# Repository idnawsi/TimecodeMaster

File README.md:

# TimecodeMaster

A wireless SMPTE linear timecode (LTC) generator for film and video sets, built from two ESP32 modules per unit. One master unit holds the time; up to ten client units are jammed to it over ESP-NOW and then run independently on their own TCXO-referenced clock. Each unit produces an LTC audio signal on a 3.5 mm jack for a camera or recorder.

This repository holds everything needed to build and run the system: the KiCad design for the master board, the firmware for all four ESP32 images, and two desktop tools for working with recorded LTC.

| Top (3D render) | Bottom (3D render) |
|---|---|
|  |  |

Board layout views (front, back, and each copper layer) are in [hardware/README.md](hardware/README.md#board-views).

## Frame rates

| Rate | Drop frame | Sample clock | Samples per LTC bit |
|---|---|---|---|
| 23.976 | no | 47952.048 Hz | 25 |
| 24 | no | 48000 Hz | 25 |
| 25 | no | 48000 Hz | 24 |
| 29.97 | selectable | 47952.048 Hz | 20 |
| 30 | no | 48000 Hz | 20 |

The non-integer rates are not approximated. The sample clock itself is divided by 1001, so the LTC frame period is exact and a whole number of samples fits in every bit cell. See [docs/timing.md](docs/timing.md).

## How it works, in short

1. A 25 MHz TCXO feeds an Si5351 clock generator. Its PLL runs at 768 MHz, and a single integer divider produces either 48000 Hz or 47952.048 Hz.
2. That clock is wired to an interrupt pin on the LTC ESP32. Every rising edge writes one sample to the DAC. The bit pattern of the current LTC frame is stepped one sample at a time, so the output frequency is the Si5351 frequency and nothing else.
3. The second ESP32 (the Utility device) runs the Wi-Fi access point and web interface, programs the Si5351, reads the RTC, and talks to the LTC device over SPI.
4. The master sends the time to each client over ESP-NOW, aligned to an LTC frame boundary. After that, every unit keeps time from its own TCXO. Wireless traffic does not steer the clock.
5. A unit can also jam-sync to an external LTC signal fed into the same 3.5 mm jack.

The full description is in [docs/how-it-works.md](docs/how-it-works.md).

The full schematic is in [hardware/docs/schematic.pdf](hardware/docs/schematic.pdf) and the board outputs in [hardware/](hardware/).

## LTC Sync App

During the shoot, each unit records the same LTC onto a camera or recorder audio channel. In post, the [LTC Sync App](docs/ltc-sync-app.md) reads that LTC from the files, places every clip on one timeline by its timecode, and exports the timeline to DaVinci Resolve, Premiere Pro or Final Cut Pro X. It reads the date and a two-digit camera ID that the units write into the LTC user bits, handles 23.976 and 29.97 exactly, and can correct per-camera offsets and a recorder's clock drift. Usage is described in [docs/ltc-sync-app.md](docs/ltc-sync-app.md).

## Repository layout

| Path | Contents |
|---|---|
| [hardware/](hardware/) | KiCad projects (main board, button boards), schematic PDF, BOM, released Gerbers, STEP models |
| [firmware/](firmware/) | Four Arduino sketches: master LTC, master Utility, client LTC, client Utility |
| [software/ltc-sync-app/](software/ltc-sync-app/) | Desktop app that reads LTC from video and audio files, aligns clips, and exports timelines |
| [software/ltc-analyzer/](software/ltc-analyzer/) | Desktop tool that decodes LTC from a live input or a file and reports continuity and drift |
| [docs/](docs/) | Architecture, timing, hardware notes, pinout, protocols, build and operation guides |

## Documentation

| Document | Subject |
|---|---|
| [docs/how-it-works.md](docs/how-it-works.md) | Architecture, clocking, synchronisation, jam sync, power |
| [docs/timing.md](docs/timing.md) | LTC format, non-integer frame rates, drop frame, drift budget |
| [docs/hardware.md](docs/hardware.md) | Circuit description of the master board |
| [docs/pinout.md](docs/pinout.md) | GPIO assignments for every ESP32 image, connector pinouts |
| [docs/protocol.md](docs/protocol.md) | SPI link, ESP-NOW messages, HTTP and WebSocket interface |
| [docs/firmware.md](docs/firmware.md) | Toolchain, libraries, build, first flash, over-the-air updates |
| [docs/operation.md](docs/operation.md) | Pairing, syncing, buttons, jam sync, battery, troubleshooting |
| [docs/ltc-sync-app.md](docs/ltc-sync-app.md) | Using the LTC Sync App to align footage and export timelines |
| [docs/design-notes.md](docs/design-notes.md) | Why the classic ESP32 was used (cost and the DAC), why the DAC ended up unused, and what an ESP32-S3 would change |
| [docs/field-test.md](docs/field-test.md) | One real shoot: what the LTC Sync App read from the files |
| [docs/security.md](docs/security.md) | Wi-Fi password, web interface, ESP-NOW and OTA: what is and is not protected |
| [hardware/README.md](hardware/README.md) | Design files, BOM, fabrication status |

## Quick start

Requirements: Arduino IDE 2.x or `arduino-cli`, the `esp32` board package (3.x), and the libraries listed in [docs/firmware.md](docs/firmware.md).

1. Build and flash the two master images (`master_LTC_Device_Jamsync` to the LTC module, `Master_Utility_Device_JamSync_Wireless` to the Utility module). Use board "ESP32 Dev Module" and the "Default 4MB with spiffs" partition scheme.
2. Build and flash the two client images the same way (`Client_LTC_Device`, `Client_Utility_Device_Wireless`).
3. Power the master. Join the Wi-Fi network `TimecodeMaster-XXXX`, open `http://192.168.4.1`, and start pairing.
4. Power a client, confirm it on the master page, and press Sync.

Details, including the password and button gestures, are in [docs/operation.md](docs/operation.md).

## Status

- Firmware version 1.3.37 for the master Utility image and 1.3.34 for the other three. See [CHANGELOG.md](CHANGELOG.md).
- The main board is now Rev 4.2. The KiCad sources in `hardware/kicad/main-board` and the Gerbers in `hardware/fabrication/main-board-rev4.2` are Rev 4.2; the Rev 4.2 set has not been used for an order yet. The released Rev 4.1 Gerbers are kept in `hardware/fabrication/main-board-rev4.1`. See [hardware/README.md](hardware/README.md).
- The current KiCad source adds an ESD diode (D4) and a series resistor (R48) on the LTC I/O jack. The Rev 4.1 Gerbers do not include them; the Rev 4.2 set does. The microphone jack and the LTC jack's ring contact are not protected.
- Only the master board has a PCB design in this repository. The client firmware targets the same two-ESP32 architecture, but its Utility image uses a few different GPIOs (see [docs/pinout.md](docs/pinout.md)).
- The firmware has little security. The web interface has no login, ESP-NOW is unencrypted, and the OTA password is a fixed string. See [docs/security.md](docs/security.md).
- The firmware has not been certified against any broadcast standard. Check the output against your own equipment, for example with the LTC Analyzer in this repository.

## Authorship

The firmware in this repository was written by AI. The hardware (schematic and PCB) was designed by me, and the testing of the units was done by me. Read the firmware with that in mind and check it on your own hardware before relying on it.

## License

Source-available under the [PolyForm Noncommercial License 1.0.0](LICENSE), with an [additional permission](ADDITIONAL-PERMISSION.md). Personal, hobby, study and other noncommercial use is free. Small independent users (total business revenue under US$100,000 a year, for example photographers, videographers and indie filmmakers) may also use it on their own paid work for free. Everyone else using it commercially, and anyone selling or renting units, boards, firmware or software, needs a separate paid license. See [COMMERCIAL.md](COMMERCIAL.md). This is not an OSI-approved open source license.

Required notice: see [NOTICE](NOTICE). Material from other people (KiCad and part libraries, the libraries the firmware needs) keeps its own terms; see [THIRD-PARTY.md](THIRD-PARTY.md).

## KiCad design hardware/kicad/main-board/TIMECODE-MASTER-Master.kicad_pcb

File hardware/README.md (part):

# Hardware

KiCad 9 design files, outputs and manufacturing data for the TimecodeMaster main board and its two small accessory boards. The circuit is described in [../docs/hardware.md](../docs/hardware.md) and the pin assignments in [../docs/pinout.md](../docs/pinout.md).

The schematic as a PDF: [docs/schematic.pdf](docs/schematic.pdf). Board views are below.

## Board views

3D renders from KiCad (top and bottom):

| Top | Bottom |
|---|---|
|  |  |

Layout views (copper, mask and silkscreen). The back view is mirrored, as seen from the back of the board:

Individual copper layers (the back layer is mirrored):

| Front (F.Cu) | Inner 1 (In1.Cu) |
|---|---|
|  |  |

| Inner 2 (In2.Cu) | Back (B.Cu) |
|---|---|
|  |  |

All views come from the current PCB source (Rev 4.2), not from the Rev 4.1 Gerbers (see Fabrication status below).

## Contents

| Path | Contents |
|---|---|
| `kicad/main-board/` | Project, schematic and PCB of the master board (title block "TimeCode-Master") |
| `kicad/control-button-board/` | Four tactile switches (FPS, LEVEL, WIFI, SYNC) and the 5-pin connector that plugs into J4 |
| `kicad/power-switch-board/` | The slide power switch (TL2285EE) on the `G-Switch` net |
| `fabrication/main-board-rev4.1/` | Gerber and drill files of the released Rev 4.1 boards, generated 2026-02-10 with KiCad 9.0.5 |
| `fabrication/main-board-rev4.2/` | Gerber and drill files of Rev 4.2, plotted from the current source on 2026-11-20 with KiCad 9.0.5 |
| `fabrication/control-button-board/`, `fabrication/power-switch-board/` | Gerber and drill files for the accessory boards |
| `cad/` | STEP models of the main board and the button boards |
| `docs/` | Schematic (PDF, SVG) and board renders |
| `bom.csv` | Bill of materials for the main board, generated from the schematic |
| `scripts/` | `export.sh` regenerates the PDF, SVG, renders and BOM; `make_bom.py` builds the BOM from a netlist |

## Board

| Item | Value |
|---|---|
| Size | 70.04 x 50.54 mm |
| Layers | 4 (F.Cu, In1.Cu, In2.Cu, B.Cu), 1.6 mm |
| Minimum track / space (released Gerbers) | 0.127 mm |
| Main parts | 2 x ESP32-WROOM-32E, Si5351A, 25 MHz TCXO, DS3231M, ADS1115, TPS63070, TP4056, OPA365 |
| Mounting | 4 x M2.5 holes |

Symbols and footprints, including the custom ones (TSX-3225, SMF05C, PJ-342B, the RGB LED, the TL2285EE switch), are embedded in the schematic and board files.

## Fabrication status

Two Gerber sets are kept:

- `fabrication/main-board-rev4.1` was released on 2026-02-10. It does not match the current source and is kept for reference.
- `fabrication/main-board-rev4.2` is Rev 4.2, plotted from the current source in `kicad/main-board` on 2026-11-20 (4 layers, 70.04 x 50.54 mm, outline unchanged). The board silkscreen reads Rev4.2. The set has not been used for an order.

What changed from Rev 4.1 to Rev 4.2:

- D4 (ESD diode) and R48 (1 kOhm) on the LTC I/O jack, and the OPA365 (U16) instead of the OPA1656.
- The 10 uF radial capacitors C18 and C21 now have a 1.5 mm lead pitch and 0.6 mm holes (Rev 4.1: 2.5 mm pitch, 0.8 mm holes). Buy 4 mm radial capacitors with 1.5 mm leads.
- The via drill mix differs (0.33 mm now appears, 50 holes), and the plated hole count went from 387 to 414.
- A stray 100 nF footprint labelled C28 was removed.

Before ordering from either set:

1. Open `kicad/main-board/TIMECODE-MASTER-Master.kicad_pcb` and run the design rule check (13 items today, listed below).
2. Re-plot if you change anything (the commands are in `scripts/export.sh`). Check the files in a Gerber viewer and with your manufacturer's own checker.
3. The BOM, pin tables and schematic PDF in this repository match Rev 4.2, not Rev 4.1.

## Known limitations

The design is published as it stands. These are the open points, recorded so that nobody has to find them again.

- **Jack protection is partial.** The current source has an ESD diode (D4, PESD5V0S1BA) and a 1 kOhm series resistor (R48) on the tip of the LTC I/O jack. The ring contact of that jack (U14 pin 3, through S1) and the microphone jack U13 have no protection. The Rev 4.1 boards have none of it.
- **Rev 4.1 and Rev 4.2 differ.** The Gerbers in `fabrication/main-board-rev4.1` are the Rev 4.1 set; Rev 4.2 has its own (see Fabrication status). Rev 4.2 adds D4 and R48 and replaces the OPA1656 microphone preamp with an OPA365 (U16). The OPA1656 needs at least 4.5 V and runs from a 3.3 V rail on Rev 4.1; the microphone path is not used by the firmware, so nothing depends on it.
- **MIC output level.** It is set by a resistor divider and cannot be changed in firmware. R48 takes roughly 1 to 3 dB off it. Raise the camera gain or change R16 if a camera needs more.
- **Design rule check.** 13 items: 11 copper-to-edge clearance (corner mounting holes and R10 on the back) and 2 courtyard overlaps (U12 with MH1, D4 with U10).
- **Q1 and Q2** drive CD4066 control pins with no pull-down, and the Utility wake divider gives 2.5 V. See [docs/hardware.md](../docs/hardware.md).

## Bill of materials (main board)

Generated from the current schematic by `scripts/make_bom.py`. Passive values are as drawn; confirm tolerances and voltage ratings when sourcing. The part list contains no manufacturer part numbers for passives.

| Qty | References | Value | Footprint | Function |
|---:|---|---|---|---|
| 1 | U1 | CD4066BM | SO-14_3.9x8.65mm_P1.27mm | Quad analog switch (LINE/MIC level, LTC jack direction) |
| 1 | U2 | SMF05CT1G | SOT65P210X110-6N | USB ESD / TVS array |
| 1 | U3 | DS3231M | SOIC-16W_7.5x10.3mm_P1.27mm | Real-time clock with integrated TCXO |
| 1 | U4 | 74HC14 | SOIC-14_3.9x8.7mm_P1.27mm | Hex Schmitt-trigger inverter (LTC output buffer, input conditioning) |
| 1 | U5 | TP4056-42-ESOP8 | SOIC-8-1EP_3.9x4.9mm_P1.27mm_EP2.41x3.3mm_ThermalVias | Li-ion linear charger, 1 A max |
| 1 | U6 | FS8205A-SOT23 | TSOT-23-6_HandSoldering | Dual N-channel MOSFET (battery protection switch) |
| 1 | U7 | DW01A | SOT-23-6 | Li-ion protection controller |
| 1 | U8 | RT9013-33GB | SOT94P279X129-5N | 3.3 V LDO (500 mA), analog rail |
| 1 | U10 | LTC-DEVICE | ESP32-WROOM-32E | ESP32-WROOM-32E module: LTC device |
| 1 | U11 | TPS63070RNMR | VREG_TPS63070RNMR | Buck-boost converter, 3.3 V system rail |
| 1 | U12 | UTILITY-DEVICE | ESP32-WROOM-32E | ESP32-WROOM-32E module: Utility device |
| 2 | U13, U14 | PJ-342B | PJ-342B | 3.5 mm jacks: U13 microphone output, U14 LTC I/O |
| 1 | U15 | ADS1115IDGS | TSSOP-10_3x3mm_P0.5mm | 16-bit I2C ADC (battery voltage) |
| 1 | U16 | OPA365xxDBV | SOT-23-5 | Single rail-to-rail op-amp, 2.2 to 5.5 V (microphone preamp) |
| 1 | X1 | 25MHZ 0.5ppm TCXO | TSX-3225 | 25 MHz 0.5 ppm TCXO |
| 1 | Y1 | Si5351A-B-GT | MSOP-10_3x3mm_P0.5mm | I2C programmable clock generator |
| 4 | Q1-Q4 | AO3407 | SOT-23 | P-channel MOSFET, SOT-23 (Q1, Q2 level control; Q3 power switch; Q4 battery path) |
| 1 | D1 | OSTB0805C1C-A | LEDSC200X125X110-4N | Bi-colour LED (charge / standby) |
| 1 | D2 | SS14 | D_SMA | Schottky diode (USB to supply OR-ing) |
| 1 | D3 | Blue_Led | LED_0805_2012Metric | Blue status LED (Utility GPIO2) |
| 1 | D4 | PESD5V0S1BA | D_SOD-323 | Bidirectional ESD diode on the LTC jack tip (R48 limits current behind it) |
| 1 | J1 | USB_C_Receptacle_PowerOnly_6P | USB_C_Receptacle_HRO_TYPE-C-31-M-17 | USB-C receptacle, power only |
| 1 | J2 | S8421-45R | 2 Pad | RTC backup battery pads |
| 1 | J3 | SSD1306 oled | 4 Pad | OLED connector (SSD1306, I2C) |
| 1 | J4 | Conn_01x05_MountingPin | JST_PH_S5B-PH-SM4-TB_1x05-1MP_P2.00mm_Horizontal | Button board connector |
| 1 | S1 | SSSS811101 | SW_SSSS811101 | Slide switch (jack routing) |
| 1 | L1 | 1.5uH | L_7.3x7.3_H4.5 | 1.5 uH power inductor |
| 13 | C1, C3, C4, C6, C10, C13-C15, C19, C22, C25-C27 | 100nF | C_0402_1005Metric_Pad0.74x0.62mm_HandSolder | Capacitor |
| 5 | C2, C5, C9, C12, C16 | 10uF | C_0805_2012Metric | Capacitor |
| 1 | C7 | 10uF | C_0805_2012Metric_Pad1.18x1.45mm_HandSolder | Capacitor |
| 1 | C8 | 10nF | C_0805_2012Metric | Capacitor |
| 3 | C11, C29, C31 | 22uF | C_0805_2012Metric_Pad1.18x1.45mm_HandSolder | Capacitor |
| 1 | C17 | 10uF | C_0402_1005Metric_Pad0.74x0.62mm_HandSolder | Capacitor |
| 2 | C18, C21 | 10uf | C_Radial_D4.0mm_H5.0mm_P1.50mm | Capacitor |
| 1 | C20 | 10pf | C_0402_1005Metric_Pad0.74x0.62mm_HandSolder | Capacitor |
| 2 | C23, C24 | 100uF | CP_EIA-3528-21_Kemet-B_HandSolder | Capacitor |
| 1 | C28 | 1uF | C_0402_1005Metric_Pad0.74x0.62mm_HandSolder | Capacitor |
| 1 | C30 | 1000uF | CP_Elec_8x10 | Capacitor |
| 8 | R1, R3, R25, R26, R39, R43, R44, R47 | 4.7k | R_0402_1005Metric_Pad0.72x0.64mm_HandSolder | Resistor |
| 2 | R2, R4 | 5K1 | R_0402_1005Metric_Pad0.72x0.64mm_HandSolder | Resistor |
| 5 | R5, R8, R14, R16, R48 | 1K | R_0402_1005Metric_Pad0.72x0.64mm_HandSolder | Resistor |
| 6 | R6, R27, R35, R37, R40, R41 | 100k | R_0402_1005Metric_Pad0.72x0.64mm_HandSolder | Resistor |
| 1 | R7 | 68K | R_0402_1005Metric_Pad0.72x0.64mm_HandSolder | Resistor |
| 10 | R9, R18, R19, R23, R28, R30, R31, R33, R45, R46 | 20k | R_0402_1005Metric_Pad0.72x0.64mm_HandSolder | Resistor |
| 1 | R10 | 1.2K | R_0402_1005Metric_Pad0.72x0.64mm_HandSolder | Resistor |
| 1 | R11 | 10R | R_0805_2012Metric | Resistor |
| 1 | R12 | 100R | R_0805_2012Metric | Resistor |
| 2 | R13, R15 | 15K | R_0402_1005Metric_Pad0.72x0.64mm_HandSolder | Resistor |
| 2 | R17, R34 | 10k | R_0402_1005Metric_Pad0.72x0.64mm_HandSolder | Resistor |
| 1 | R20 | 47K | R_0402_1005Metric_Pad0.72x0.64mm_HandSolder | Resistor |
| 1 | R21 | 20R | R_0402_1005Metric_Pad0.72x0.64mm_HandSolder | Resistor |
| 1 | R22 | 100K | R_0402_1005Metric | Resistor |
| 2 | R24, R42 | 10k | R_0402_1005Metric | Resistor |
| 1 | R29 | 150k | R_0402_1005Metric_Pad0.72x0.64mm_HandSolder | Resistor |
| 1 | R32 | 470k | R_0402_1005Metric_Pad0.72x0.64mm_HandSolder | Resistor |
| 1 | R36 | 100R | R_0402_1005Metric_Pad0.72x0.64mm_HandSolder | Resistor |
| 1 | R38 | 47R | R_0402_1005Metric_Pad0.72x0.64mm_HandSolder | Resistor |
| 1 | BT1 | Battery_Cell | 2 Pad | Li-ion cell |
| 3 | FB1-FB3 | 600Ohm/1Mhz | L_0603_1608Metric_Pad1.05x0.95mm_HandSolder | Ferrite bead |
| 1 | JP1 | SolderJumper_2_Open | SolderJumper-2_P1.3mm_Open_Pad1.0x1.5mm | Solder jumper: converter power-save mode |
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
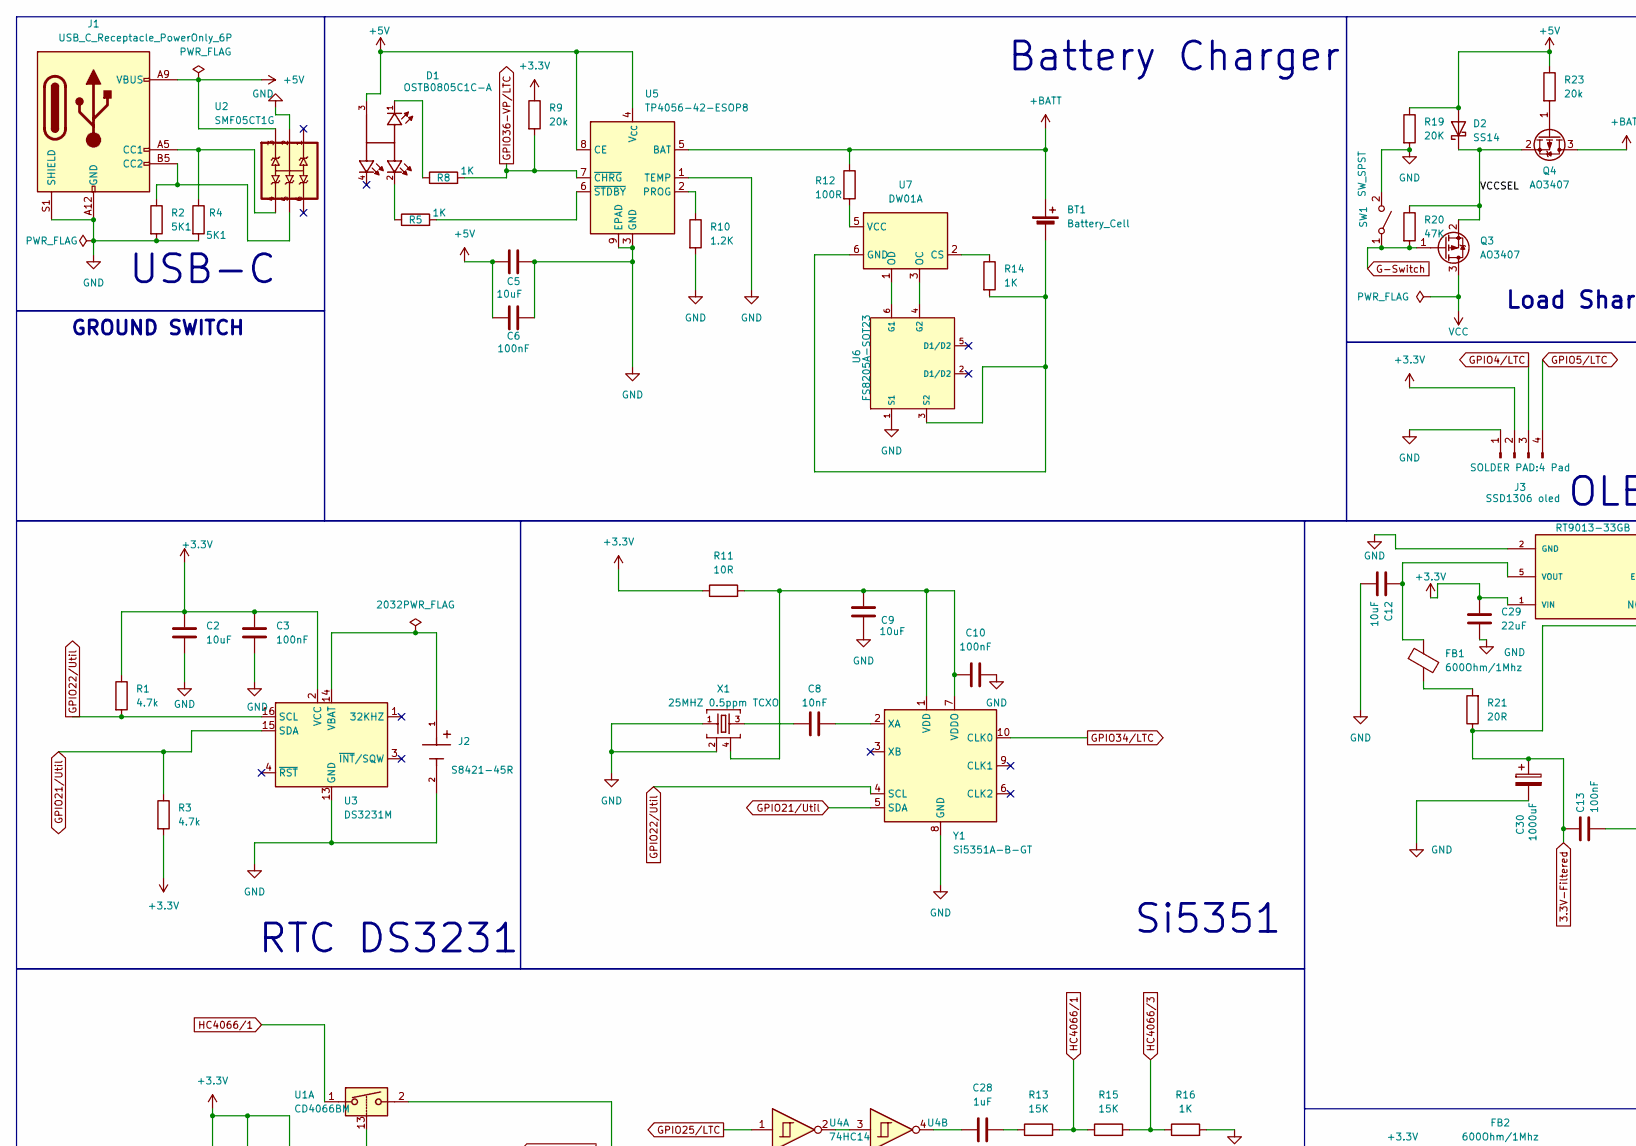
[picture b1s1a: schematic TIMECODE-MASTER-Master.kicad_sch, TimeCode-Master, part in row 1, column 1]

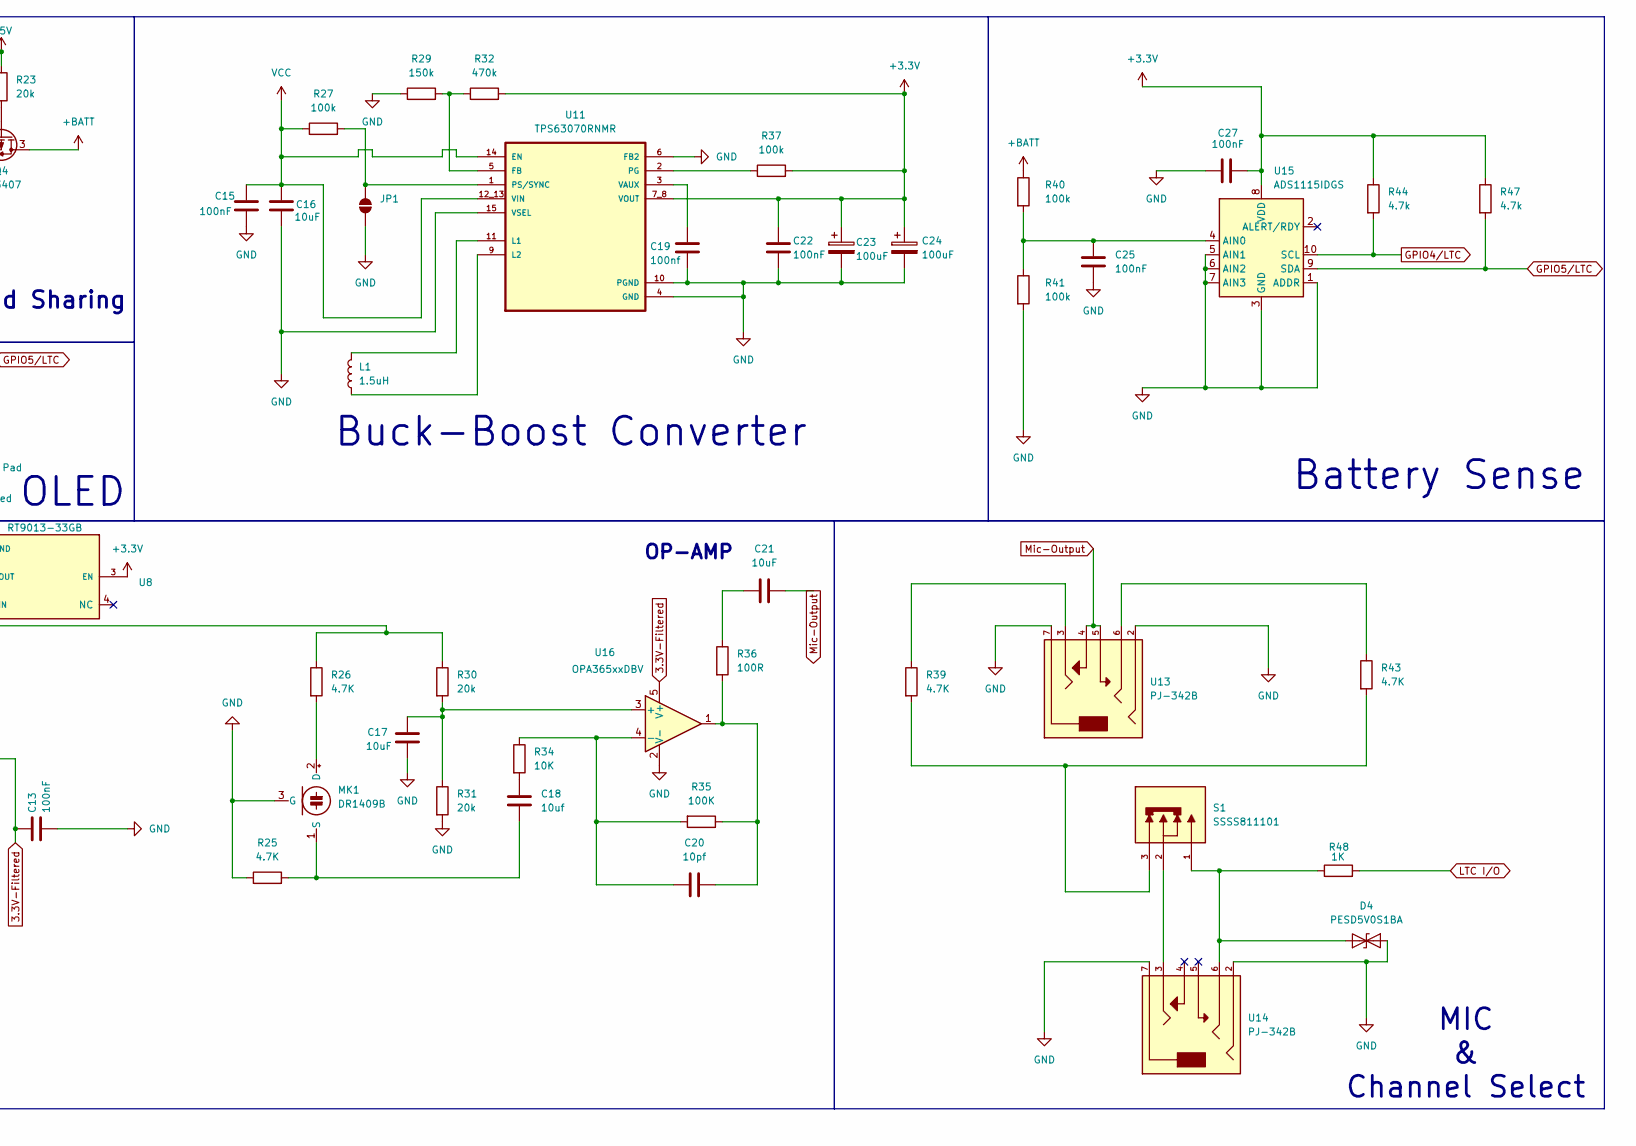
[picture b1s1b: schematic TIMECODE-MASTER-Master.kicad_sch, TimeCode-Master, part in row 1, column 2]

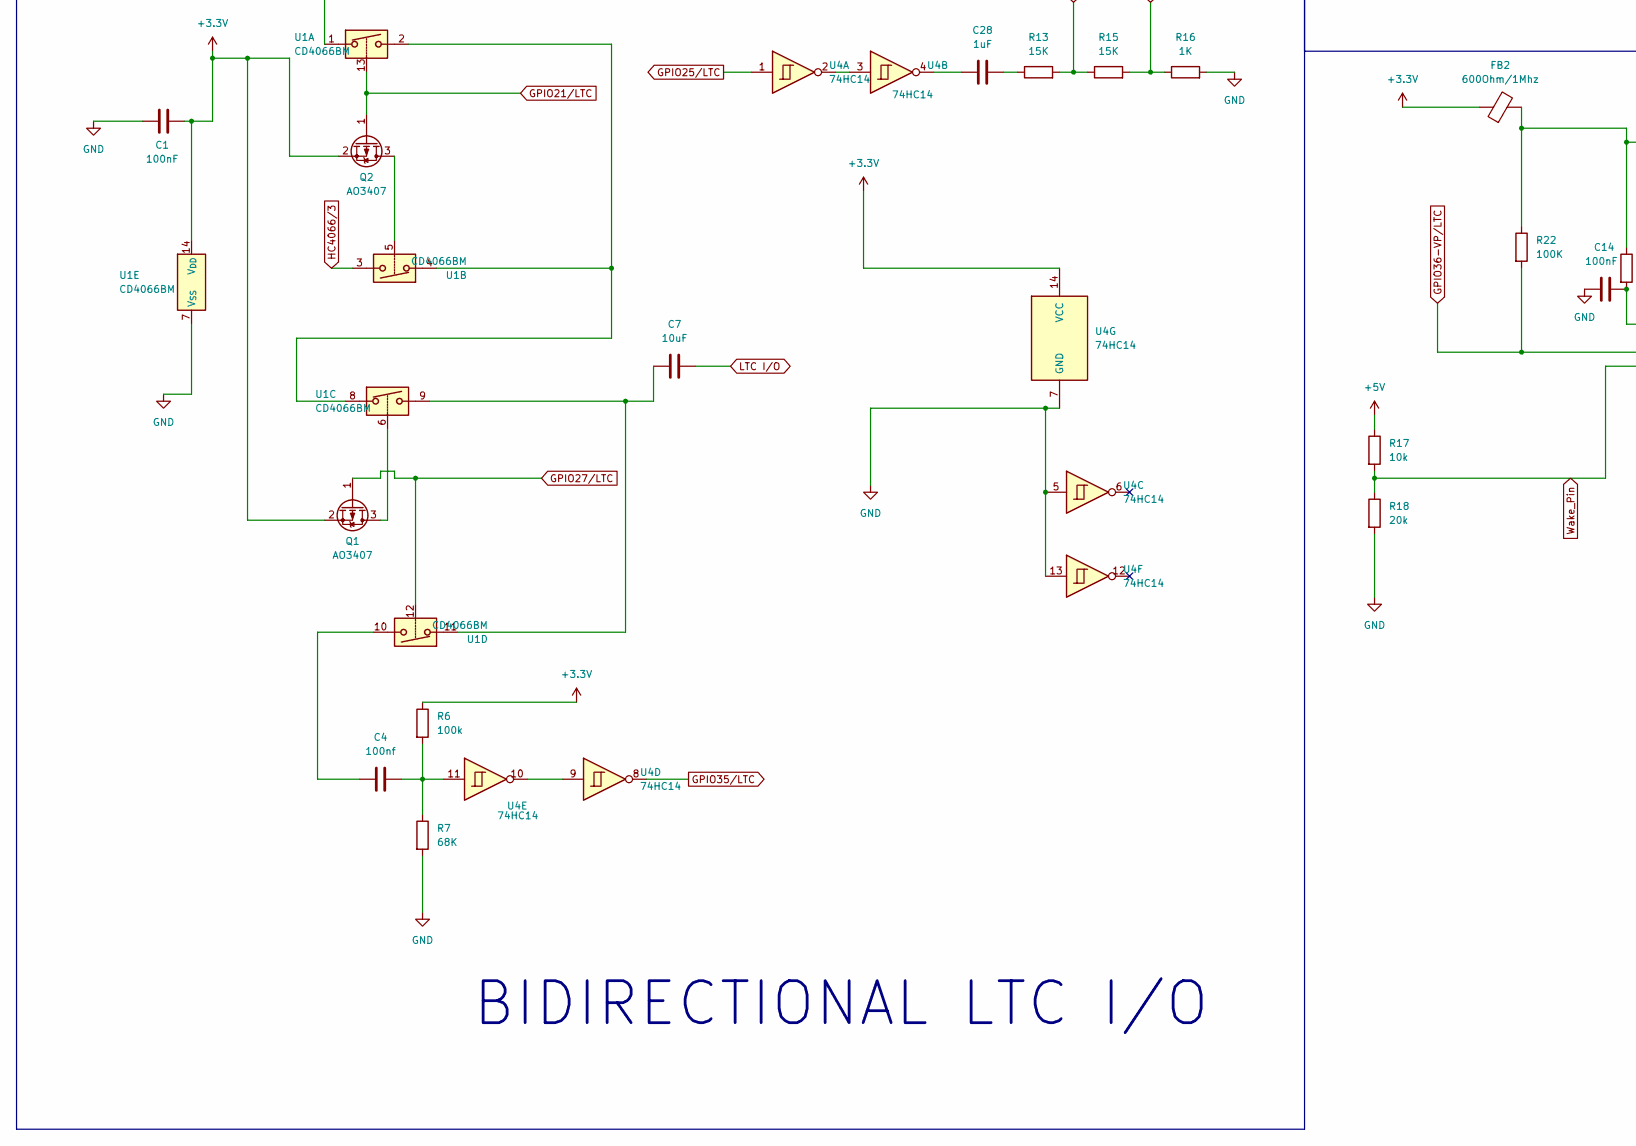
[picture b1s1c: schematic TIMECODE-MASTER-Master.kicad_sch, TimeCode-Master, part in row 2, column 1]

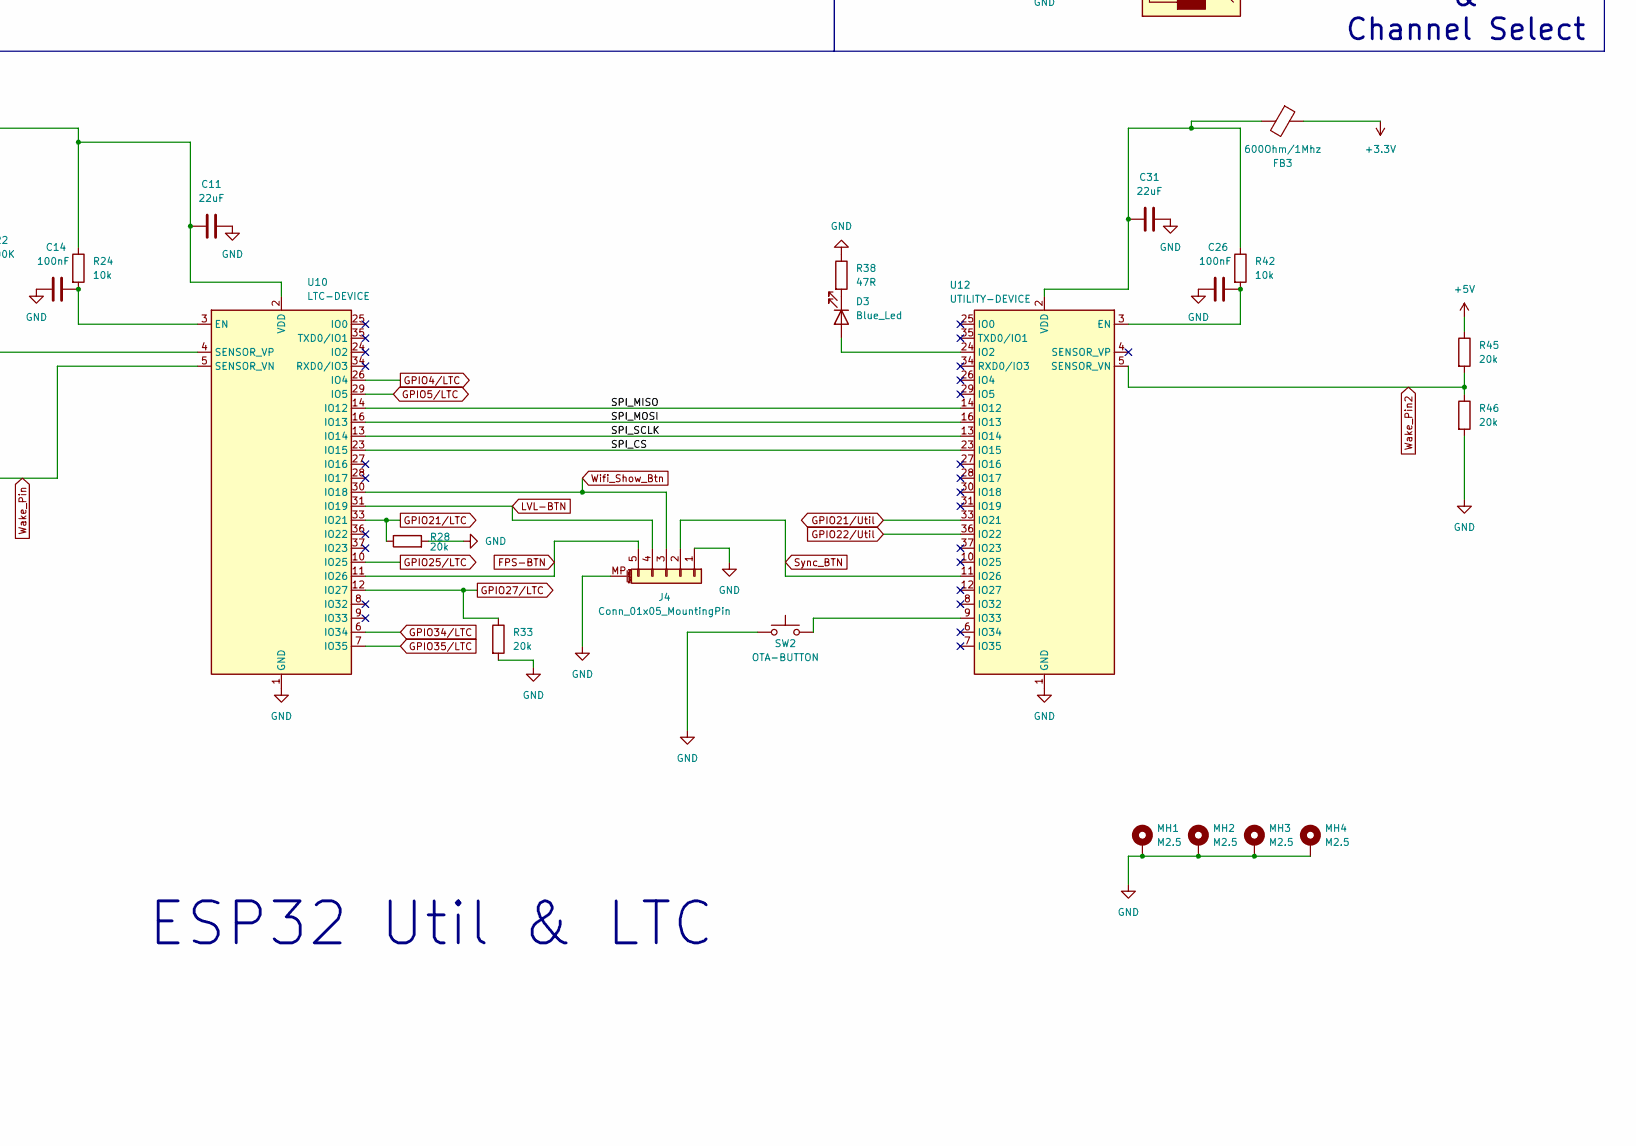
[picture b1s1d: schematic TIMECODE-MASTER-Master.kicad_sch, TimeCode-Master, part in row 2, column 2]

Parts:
BT1: Battery_Cell; 2 Pad
C1, C3, C6, C10, C13, C14, C15, C22, C25, C26, C27: 100nF; C_0402_1005Metric_Pad0.74x0.62mm_HandSolder
C2, C5, C9, C12, C16: 10uF; C_0805_2012Metric
C4, C19: 100nf; C_0402_1005Metric_Pad0.74x0.62mm_HandSolder
C7: 10uF; C_0805_2012Metric_Pad1.18x1.45mm_HandSolder
C8: 10nF; C_0805_2012Metric
C11, C29, C31: 22uF; C_0805_2012Metric_Pad1.18x1.45mm_HandSolder
C17: 10uF; C_0402_1005Metric_Pad0.74x0.62mm_HandSolder
C18: 10uf; C_Radial_D4.0mm_H5.0mm_P1.50mm
C20: 10pf; C_0402_1005Metric_Pad0.74x0.62mm_HandSolder
C21: 10uF; C_Radial_D4.0mm_H5.0mm_P1.50mm
C23, C24: 100uF; CP_EIA-3528-21_Kemet-B_HandSolder
C28: 1uF; C_0402_1005Metric_Pad0.74x0.62mm_HandSolder
C30: 1000uF; CP_Elec_8x10
D1: OSTB0805C1C-A; LEDSC200X125X110-4N
D2: SS14; D_SMA
D3: Blue_Led; LED_0805_2012Metric
D4: PESD5V0S1BA; D_SOD-323
FB1, FB2, FB3: 600Ohm/1Mhz; L_0603_1608Metric_Pad1.05x0.95mm_HandSolder
J1: USB_C_Receptacle_PowerOnly_6P; USB_C_Receptacle_HRO_TYPE-C-31-M-17
J2: S8421-45R; 2 Pad; PARTREV 7
J3: SSD1306 oled; 4 Pad
J4: Conn_01x05_MountingPin; JST_PH_S5B-PH-SM4-TB_1x05-1MP_P2.00mm_Horizontal
JP1: SolderJumper_2_Open; SolderJumper-2_P1.3mm_Open_Pad1.0x1.5mm
L1: 1.5uH; L_7.3x7.3_H4.5
MH1, MH2, MH3, MH4: M2.5; MountingHole_2.5mm_Pad_Via
MK1: DR1409B; 3 Pad
Q1, Q2, Q3, Q4: AO3407; SOT-23
R1, R3, R44, R47: 4.7k; R_0402_1005Metric_Pad0.72x0.64mm_HandSolder
R2, R4: 5K1; R_0402_1005Metric_Pad0.72x0.64mm_HandSolder
R5, R8, R14, R16, R48: 1K; R_0402_1005Metric_Pad0.72x0.64mm_HandSolder
R6, R27, R37, R40, R41: 100k; R_0402_1005Metric_Pad0.72x0.64mm_HandSolder
R7: 68K; R_0402_1005Metric_Pad0.72x0.64mm_HandSolder
R9, R18, R23, R28, R30, R31, R33, R45, R46: 20k; R_0402_1005Metric_Pad0.72x0.64mm_HandSolder
R10: 1.2K; R_0402_1005Metric_Pad0.72x0.64mm_HandSolder
R11: 10R; R_0805_2012Metric
R12: 100R; R_0805_2012Metric
R13, R15: 15K; R_0402_1005Metric_Pad0.72x0.64mm_HandSolder
R17: 10k; R_0402_1005Metric_Pad0.72x0.64mm_HandSolder
R19: 20K; R_0402_1005Metric_Pad0.72x0.64mm_HandSolder
R20: 47K; R_0402_1005Metric_Pad0.72x0.64mm_HandSolder
R21: 20R; R_0402_1005Metric_Pad0.72x0.64mm_HandSolder
R22: 100K; R_0402_1005Metric
R24, R42: 10k; R_0402_1005Metric
R25, R26, R39, R43: 4.7K; R_0402_1005Metric_Pad0.72x0.64mm_HandSolder
R29: 150k; R_0402_1005Metric_Pad0.72x0.64mm_HandSolder
R32: 470k; R_0402_1005Metric_Pad0.72x0.64mm_HandSolder
R34: 10K; R_0402_1005Metric_Pad0.72x0.64mm_HandSolder
R35: 100K; R_0402_1005Metric_Pad0.72x0.64mm_HandSolder
R36: 100R; R_0402_1005Metric_Pad0.72x0.64mm_HandSolder
R38: 47R; R_0402_1005Metric_Pad0.72x0.64mm_HandSolder
S1: SSSS811101; SW_SSSS811101; PARTREV N/A
SW1: SW_SPST; 2 Pad
SW2: OTA-BUTTON; SMD-SIDE SWITCH
U1: CD4066BM; SO-14_3.9x8.65mm_P1.27mm
U2: SMF05CT1G; SOT65P210X110-6N
U3: DS3231M; SOIC-16W_7.5x10.3mm_P1.27mm
U4: 74HC14; SOIC-14_3.9x8.7mm_P1.27mm
U5: TP4056-42-ESOP8; SOIC-8-1EP_3.9x4.9mm_P1.27mm_EP2.41x3.3mm_ThermalVias
U6: FS8205A-SOT23; TSOT-23-6_HandSoldering
U7: DW01A; SOT-23-6
U8: RT9013-33GB; SOT94P279X129-5N; PARTREV Aprill 2011
U10: LTC-DEVICE; ESP32-WROOM-32E
U11: TPS63070RNMR; VREG_TPS63070RNMR
U12: UTILITY-DEVICE; ESP32-WROOM-32E
U13, U14: PJ-342B
U15: ADS1115IDGS; TSSOP-10_3x3mm_P0.5mm
U16: OPA365xxDBV; SOT-23-5
X1: 25MHZ 0.5ppm TCXO; TSX-3225
Y1: Si5351A-B-GT; MSOP-10_3x3mm_P0.5mm

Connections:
3.3V-Filtered: C13.1, C30.1, R21.1, R26.1, R30.1, U16.5 (V+)
+3.3V: C1.2, C2.1, C3.1, C22.1, C23.1, C24.1, C27.2, C29.1, FB2.1, FB3.1, J3.2, Q1.2 (S), Q2.2 (S), R1.1, R3.2, R6.1, R9.1, R11.1, R32.2, R37.2, R44.1, R47.1, U1.14 (V_{DD}), U3.2 (VCC), U4.14 (VCC), U8.1 (VIN), U8.3 (EN), U11.7_8 (VOUT), U15.8 (VDD)
+5V: C5.1, C6.1, D1.3, D2.2 (A), J1.A9 (VBUS), J1.B9 (VBUS), R17.1, R19.1, R23.1, R45.1, U2.3, U5.4 (V_{CC}), U5.8 (CE)
+BATT: BT1.1 (+), Q4.3 (D), R12.1, R40.1, U5.5 (BAT)
/SPI_CS: U10.23 (IO15), U12.23 (IO15)
/SPI_MISO: U10.14 (IO12), U12.14 (IO12)
/SPI_MOSI: U10.16 (IO13), U12.16 (IO13)
/SPI_SCLK: U10.13 (IO14), U12.13 (IO14)
/VCCSEL: D2.1 (K), Q3.2 (S), Q4.2 (S), R20.1
FPS-BTN: J4.5, U10.11 (IO26)
G-Switch: Q3.1 (G), R20.2, SW1.1 (A)
GND: C1.1, C2.2, C3.2, C5.2, C6.2, C9.2, C10.2, C11.2, C12.2, C13.2, C14.1, C15.2, C16.2, C17.2, C19.2, C22.2, C23.2, C24.2, C25.2, C26.1, C27.1, C29.2, C30.2, C31.2, D4.2 (A2), J1.A12 (GND), J1.B12 (GND), J1.S1 (SHIELD), J2.2, J3.1, J4.1, J4.MP (MountPin), JP1.1 (A), MH1.1, MH2.1, MH3.1, MH4.1, MK1.3 (G), R2.2, R4.2, R7.2, R10.2, R16.2, R18.2, R19.2, R25.1, R28.2, R29.1, R31.2, R33.2, R38.1, R41.2, R46.2, SW1.2 (B), SW2.1, U1.7 (V_{SS}), U2.2, U3.5 (GND), U3.6 (GND), U3.7 (GND), U3.8 (GND), U3.9 (GND), U3.10 (GND), U3.11 (GND), U3.12 (GND), U3.13 (GND), U4.5, U4.7 (GND), U4.13, U5.1 (TEMP), U5.3 (GND), U5.9 (EPAD), U6.1 (S1), U8.2 (GND), U10.1 (GND), U10.15 (GND), U10.38 (GND), U10.39 (GND), U11.4 (GND), U11.6 (FB2), U11.10 (PGND), U11.15 (VSEL), U12.1 (GND), U12.15 (GND), U12.38 (GND), U12.39 (GND), U13.2, U13.7, U14.2, U14.7, U15.1 (ADDR), U15.3 (GND), U15.5 (AIN1), U15.6 (AIN2), U15.7 (AIN3), U16.2 (V-), X1.1, X1.2, Y1.8 (GND)
GPIO4/LTC: J3.3, R44.2, U10.26 (IO4), U15.10 (SCL)
GPIO5/LTC: J3.4, R47.2, U10.29 (IO5), U15.9 (SDA)
GPIO21/LTC: Q2.1 (G), R28.1, U1.13, U10.33 (IO21)
GPIO21/Util: R3.1, U3.15 (SDA), U12.33 (IO21), Y1.5 (SDA)
GPIO22/Util: R1.2, U3.16 (SCL), U12.36 (IO22), Y1.4 (SCL)
GPIO25/LTC: U4.1, U10.10 (IO25)
GPIO27/LTC: Q1.1 (G), R33.1, U1.12, U10.12 (IO27)
GPIO34/LTC: U10.6 (IO34), Y1.10 (CLK0)
GPIO35/LTC: U4.8, U10.7 (IO35)
GPIO36-VP/LTC: R8.2, R9.2, R22.2, U5.7 (~CHRG), U10.4 (SENSOR_VP)
HC4066/1: R13.2, R15.1, U1.1
HC4066/3: R15.2, R16.1, U1.3
LTC I/O: C7.2, R48.2
LVL-BTN: J4.4, U10.31 (IO19)
Mic-Output: C21.2, U13.4, U13.5
unnamed: BT1.2 (-), R14.2, U6.3 (S2), U7.6 (GND)
unnamed: C4.1, U1.10
unnamed: C4.2, R6.2, R7.1, U4.11
unnamed: C7.1, U1.9, U1.11
unnamed: C8.1, X1.3
unnamed: C18.1, R34.2
unnamed: C20.2, R35.1, R36.2, U16.1
unnamed: C21.1, R36.1
unnamed: C28.1, U4.4
unnamed: C28.2, R13.1
unnamed: D1.1, R8.1
unnamed: D1.2, R5.1
unnamed: D3.2 (A), U12.24 (IO2)
unnamed: D3.1 (K), R38.2
unnamed: D4.1 (A1), R48.1, S1.1, U14.6
unnamed: FB1.2, R21.2
unnamed: J1.A5 (CC1), R4.1, U2.4
unnamed: J1.B5 (CC2), R2.1, U2.5
unnamed: JP1.2 (B), R27.2, U11.1 (PS/SYNC)
unnamed: MK1.2 (D), R26.2
unnamed: C18.2, MK1.1 (S), R25.2
unnamed: Q1.3 (D), U1.6
unnamed: Q2.3 (D), U1.5
unnamed: Q4.1 (G), R23.2
unnamed: R39.1, U13.3
unnamed: R39.2, R43.2, S1.3
unnamed: R43.1, U13.6
unnamed: S1.2, U14.3
unnamed: U1.2, U1.4, U1.8
unnamed: J2.1, U3.14 (VBAT)
unnamed: U4.2, U4.3
unnamed: U4.9, U4.10
unnamed: R10.1, U5.2 (PROG)
unnamed: R5.2, U5.6 (~STDBY)
unnamed: U6.6 (G1), U7.1 (OD)
unnamed: U6.4 (G2), U7.3 (OC)
unnamed: R14.1, U7.2 (CS)
unnamed: R12.2, U7.5 (VCC)
unnamed: C12.1, FB1.1, U8.5 (VOUT)
unnamed: C14.2, R24.2, U10.3 (EN)
unnamed: C11.1, FB2.2, R22.1, R24.1, U10.2 (VDD)
unnamed: R29.2, R32.1, U11.5 (FB)
unnamed: L1.2, U11.11 (L1)
unnamed: L1.1, U11.9 (L2)
unnamed: R37.1, U11.2 (PG)
unnamed: C19.1, U11.3 (VAUX)
unnamed: C26.2, R42.2, U12.3 (EN)
unnamed: SW2.2, U12.9 (IO33)
unnamed: C31.1, FB3.2, R42.1, U12.2 (VDD)
unnamed: C25.1, R40.2, R41.1, U15.4 (AIN0)
unnamed: C17.1, R30.2, R31.1, U16.3 (+)
unnamed: C20.1, R34.1, R35.2, U16.4 (-)
unnamed: C9.1, C10.1, R11.2, X1.4, Y1.1 (VDD), Y1.7 (VDDO)
unnamed: C8.2, Y1.2 (XA)
Sync_BTN: J4.2, U12.11 (IO26)
VCC: C15.1, C16.1, Q3.3 (D), R27.1, U11.12_13 (VIN), U11.14 (EN)
Wake_Pin: R17.2, R18.1, U10.5 (SENSOR_VN)
Wake_Pin2: R45.2, R46.1, U12.5 (SENSOR_VN)
Wifi_Show_Btn: J4.3, U10.30 (IO18)

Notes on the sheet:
Si5351
OP-AMP
ESP32 Util & LTC
Battery Sense
USB-C
Load Sharing
Buck-Boost Converter
RTC DS3231
BIDIRECTIONAL LTC I/O
Battery Charger
MIC & Channel Select
OLED
GROUND SWITCH

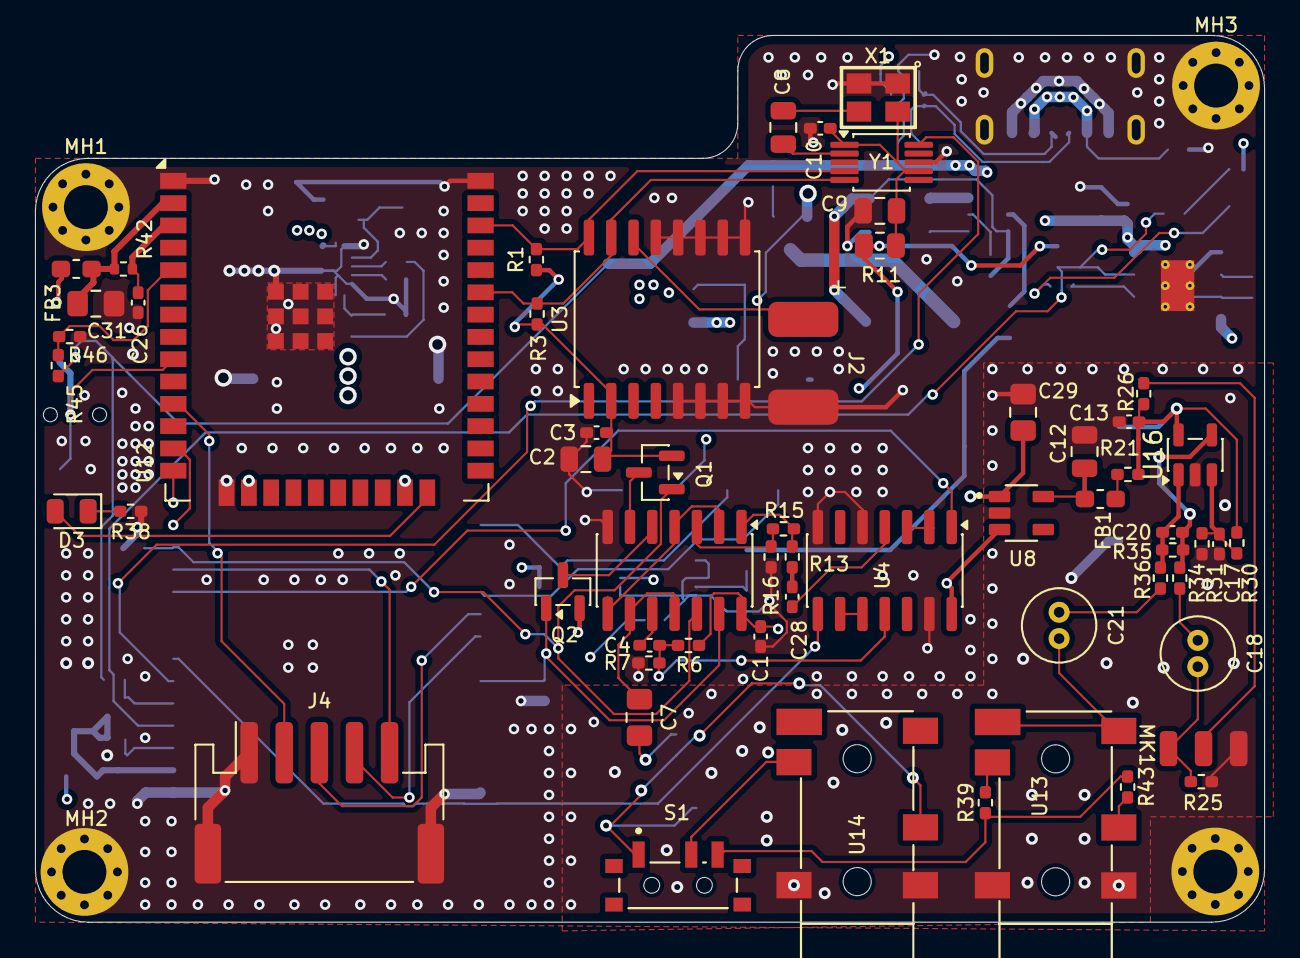
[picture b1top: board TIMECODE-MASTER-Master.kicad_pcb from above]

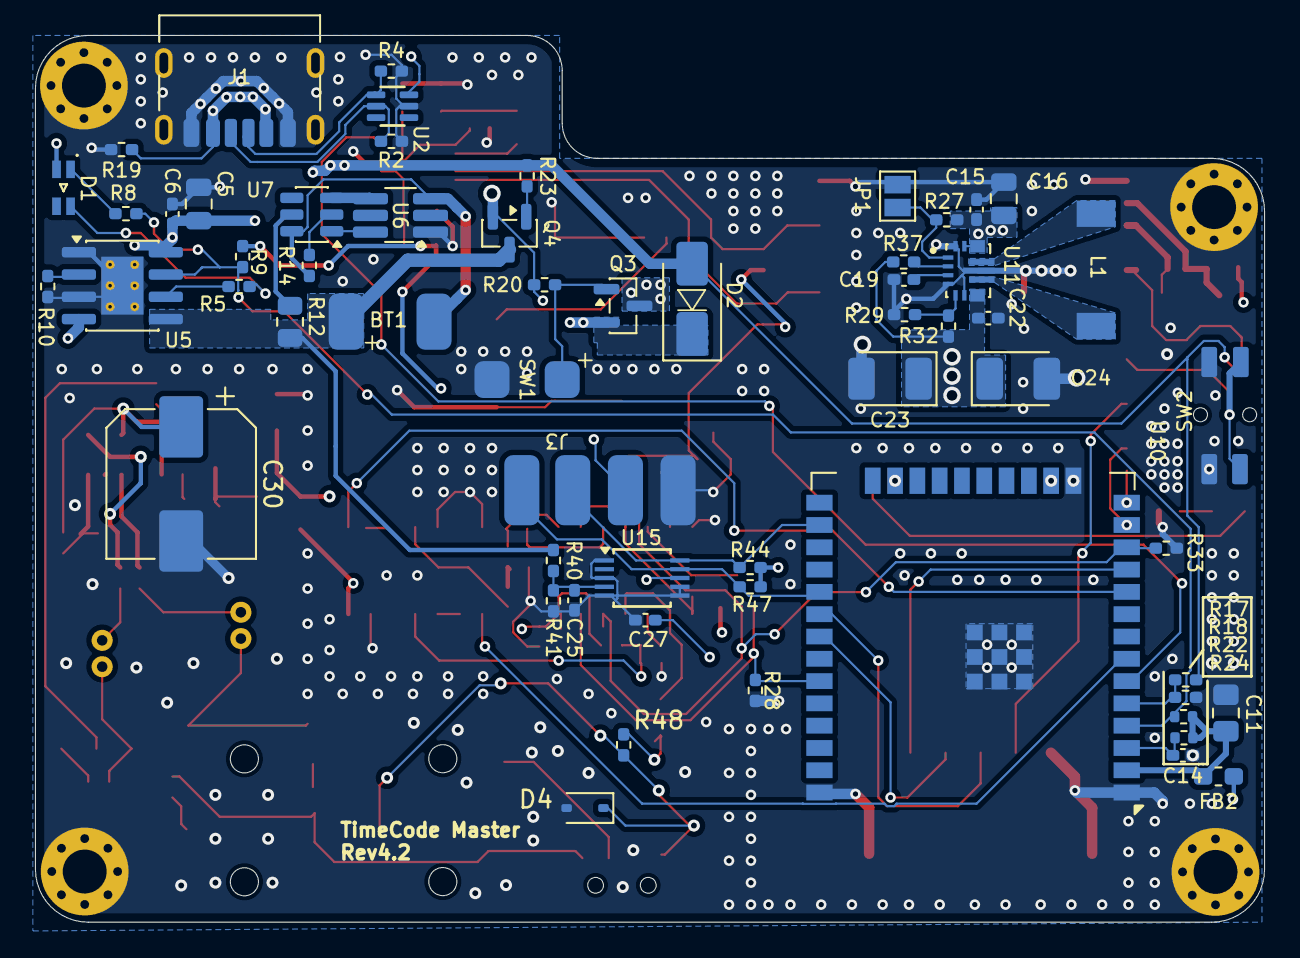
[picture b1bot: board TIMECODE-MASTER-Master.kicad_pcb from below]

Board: 4 copper layers, 70.0 x 50.5 mm, 122 parts (59 on the bottom side), 86 nets.

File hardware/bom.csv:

Qty,References,Value,Footprint,Function
1,U1,CD4066BM,SO-14_3.9x8.65mm_P1.27mm,"Quad analog switch (LINE/MIC level, LTC jack direction)"
1,U2,SMF05CT1G,SOT65P210X110-6N,USB ESD / TVS array
1,U3,DS3231M,SOIC-16W_7.5x10.3mm_P1.27mm,Real-time clock with integrated TCXO
1,U4,74HC14,SOIC-14_3.9x8.7mm_P1.27mm,"Hex Schmitt-trigger inverter (LTC output buffer, input conditioning)"
1,U5,TP4056-42-ESOP8,SOIC-8-1EP_3.9x4.9mm_P1.27mm_EP2.41x3.3mm_ThermalVias,"Li-ion linear charger, 1 A max"
1,U6,FS8205A-SOT23,TSOT-23-6_HandSoldering,Dual N-channel MOSFET (battery protection switch)
1,U7,DW01A,SOT-23-6,Li-ion protection controller
1,U8,RT9013-33GB,SOT94P279X129-5N,"3.3 V LDO (500 mA), analog rail"
1,U10,LTC-DEVICE,ESP32-WROOM-32E,ESP32-WROOM-32E module: LTC device
1,U11,TPS63070RNMR,VREG_TPS63070RNMR,"Buck-boost converter, 3.3 V system rail"
1,U12,UTILITY-DEVICE,ESP32-WROOM-32E,ESP32-WROOM-32E module: Utility device
2,"U13, U14",PJ-342B,PJ-342B,"3.5 mm jacks: U13 microphone output, U14 LTC I/O"
1,U15,ADS1115IDGS,TSSOP-10_3x3mm_P0.5mm,16-bit I2C ADC (battery voltage)
1,U16,OPA365xxDBV,SOT-23-5,"Single rail-to-rail op-amp, 2.2 to 5.5 V (microphone preamp)"
1,X1,25MHZ 0.5ppm TCXO,TSX-3225,25 MHz 0.5 ppm TCXO
1,Y1,Si5351A-B-GT,MSOP-10_3x3mm_P0.5mm,I2C programmable clock generator
4,Q1-Q4,AO3407,SOT-23,"P-channel MOSFET, SOT-23 (Q1, Q2 level control; Q3 power switch; Q4 battery path)"
1,D1,OSTB0805C1C-A,LEDSC200X125X110-4N,Bi-colour LED (charge / standby)
1,D2,SS14,D_SMA,Schottky diode (USB to supply OR-ing)
1,D3,Blue_Led,LED_0805_2012Metric,Blue status LED (Utility GPIO2)
1,D4,PESD5V0S1BA,D_SOD-323,Bidirectional ESD diode on the LTC jack tip (R48 limits current behind it)
1,J1,USB_C_Receptacle_PowerOnly_6P,USB_C_Receptacle_HRO_TYPE-C-31-M-17,"USB-C receptacle, power only"
1,J2,S8421-45R,2 Pad,RTC backup battery pads
1,J3,SSD1306 oled,4 Pad,"OLED connector (SSD1306, I2C)"
1,J4,Conn_01x05_MountingPin,JST_PH_S5B-PH-SM4-TB_1x05-1MP_P2.00mm_Horizontal,Button board connector
1,S1,SSSS811101,SW_SSSS811101,Slide switch (jack routing)
1,L1,1.5uH,L_7.3x7.3_H4.5,1.5 uH power inductor
13,"C1, C3, C4, C6, C10, C13-C15, C19, C22, C25-C27",100nF,C_0402_1005Metric_Pad0.74x0.62mm_HandSolder,Capacitor
5,"C2, C5, C9, C12, C16",10uF,C_0805_2012Metric,Capacitor
1,C7,10uF,C_0805_2012Metric_Pad1.18x1.45mm_HandSolder,Capacitor
1,C8,10nF,C_0805_2012Metric,Capacitor
3,"C11, C29, C31",22uF,C_0805_2012Metric_Pad1.18x1.45mm_HandSolder,Capacitor
1,C17,10uF,C_0402_1005Metric_Pad0.74x0.62mm_HandSolder,Capacitor
2,"C18, C21",10uf,C_Radial_D4.0mm_H5.0mm_P1.50mm,Capacitor
1,C20,10pf,C_0402_1005Metric_Pad0.74x0.62mm_HandSolder,Capacitor
2,"C23, C24",100uF,CP_EIA-3528-21_Kemet-B_HandSolder,Capacitor
1,C28,1uF,C_0402_1005Metric_Pad0.74x0.62mm_HandSolder,Capacitor
1,C30,1000uF,CP_Elec_8x10,Capacitor
8,"R1, R3, R25, R26, R39, R43, R44, R47",4.7k,R_0402_1005Metric_Pad0.72x0.64mm_HandSolder,Resistor
2,"R2, R4",5K1,R_0402_1005Metric_Pad0.72x0.64mm_HandSolder,Resistor
5,"R5, R8, R14, R16, R48",1K,R_0402_1005Metric_Pad0.72x0.64mm_HandSolder,Resistor
6,"R6, R27, R35, R37, R40, R41",100k,R_0402_1005Metric_Pad0.72x0.64mm_HandSolder,Resistor
1,R7,68K,R_0402_1005Metric_Pad0.72x0.64mm_HandSolder,Resistor
10,"R9, R18, R19, R23, R28, R30, R31, R33, R45, R46",20k,R_0402_1005Metric_Pad0.72x0.64mm_HandSolder,Resistor
1,R10,1.2K,R_0402_1005Metric_Pad0.72x0.64mm_HandSolder,Resistor
1,R11,10R,R_0805_2012Metric,Resistor
1,R12,100R,R_0805_2012Metric,Resistor
2,"R13, R15",15K,R_0402_1005Metric_Pad0.72x0.64mm_HandSolder,Resistor
2,"R17, R34",10k,R_0402_1005Metric_Pad0.72x0.64mm_HandSolder,Resistor
1,R20,47K,R_0402_1005Metric_Pad0.72x0.64mm_HandSolder,Resistor
1,R21,20R,R_0402_1005Metric_Pad0.72x0.64mm_HandSolder,Resistor
1,R22,100K,R_0402_1005Metric,Resistor
2,"R24, R42",10k,R_0402_1005Metric,Resistor
1,R29,150k,R_0402_1005Metric_Pad0.72x0.64mm_HandSolder,Resistor
1,R32,470k,R_0402_1005Metric_Pad0.72x0.64mm_HandSolder,Resistor
1,R36,100R,R_0402_1005Metric_Pad0.72x0.64mm_HandSolder,Resistor
1,R38,47R,R_0402_1005Metric_Pad0.72x0.64mm_HandSolder,Resistor
1,BT1,Battery_Cell,2 Pad,Li-ion cell
3,FB1-FB3,600Ohm/1Mhz,L_0603_1608Metric_Pad1.05x0.95mm_HandSolder,Ferrite bead
1,JP1,SolderJumper_2_Open,SolderJumper-2_P1.3mm_Open_Pad1.0x1.5mm,Solder jumper: converter power-save mode
1,MK1,DR1409B,3 Pad,Electret microphone
1,SW1,SW_SPST,2 Pad,Main power switch pads
1,SW2,OTA-BUTTON,SMD-SIDE SWITCH,OTA button
